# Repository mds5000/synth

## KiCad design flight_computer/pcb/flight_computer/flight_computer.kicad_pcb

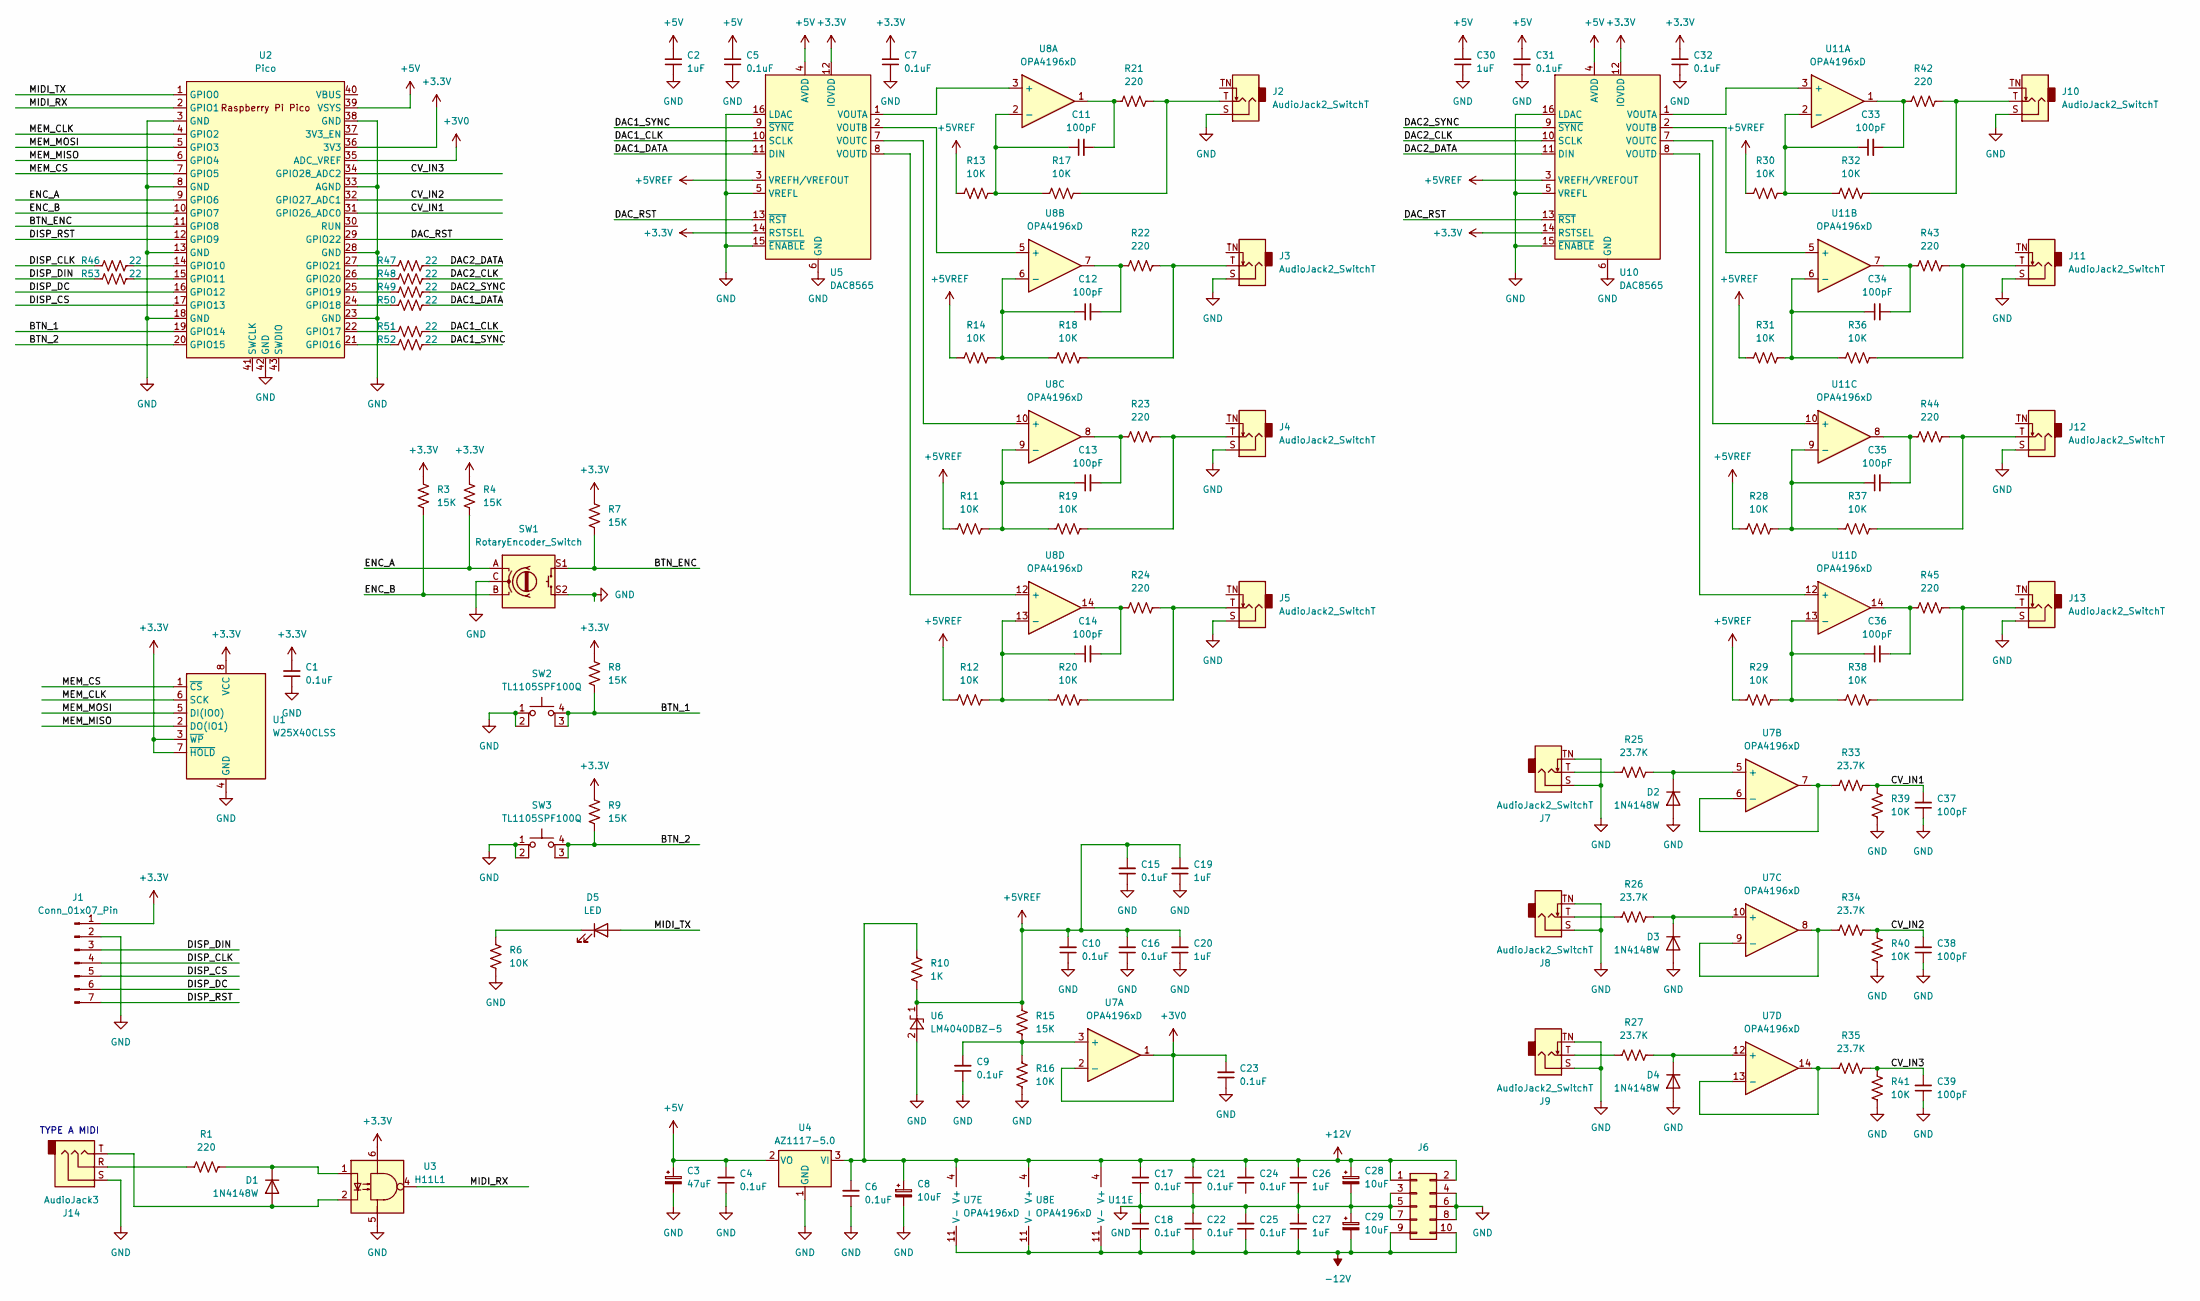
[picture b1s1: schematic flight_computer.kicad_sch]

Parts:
C1, C4, C5, C6, C7, C9, C10, C15, C16, C17, C18, C21, C22, C23, C24, C25, C31, C32: 0.1uF; C_0603_1608Metric
C2, C19, C20, C26, C27, C30: 1uF; C_0603_1608Metric
C3: 47uF; CP_Radial_D5.0mm_P2.00mm
C8, C28, C29: 10uF; CP_Radial_D5.0mm_P2.00mm
C11, C12, C13, C14, C33, C34, C35, C36, C37, C38, C39: 100pF; C_0603_1608Metric
D1, D2, D3, D4: 1N4148W; D_SOD-123
D5: LED
J1: Conn_01x07_Pin; PinHeader_1x07_P2.54mm_Vertical
J2, J3, J4, J5, J7, J8, J9, J10, J11, J12, J13: AudioJack2_SwitchT; Jack_3.5mm_QingPu_WQP-PJ398SM_Vertical_CircularHoles
J6: Conn_02x05_Odd_Even; PinHeader_2x05_P2.54mm_Vertical
J14: AudioJack3
R1, R21, R22, R23, R24, R42, R43, R44, R45: 220; R_0603_1608Metric
R3, R4, R7, R8, R9, R15: 15K; R_0603_1608Metric
R6, R11, R12, R13, R14, R16, R17, R18, R19, R20, R28, R29, R30, R31, R32, R36, R37, R38, R39, R40, R41: 10K; R_0603_1608Metric
R10: 1K; R_0603_1608Metric
R25, R26, R27, R33, R34, R35: 23.7K; R_0603_1608Metric
R46, R47, R48, R49, R50, R51, R52, R53: 22; R_0603_1608Metric
SW1: RotaryEncoder_Switch; RotaryEncoder_Alps_EC12E-Switch_Vertical_H20mm
SW2, SW3: TL1105SPF100Q; SW_PUSH_6mm_H7.3mm
U1: W25X40CLSS; SOIC-8_5.275x5.275mm_P1.27mm
U2: Pico; RPi_Pico_SMD_TH
U3: H11L1; DIP-6_W7.62mm_SMDSocket_SmallPads
U4: AZ1117-5.0; TO-252-2
U5, U10: DAC8565; TSSOP-16_4.4x5mm_P0.65mm
U6: LM4040DBZ-5; SOT-23
U7, U8, U11: OPA4196xD; SOIC-14_3.9x8.7mm_P1.27mm

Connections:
+3.3V: C1.2, C7.2, C32.2, J1.1, R3.2, R4.2, R7.2, R8.2, R9.2, U1.3 (~WP), U1.7 (~HOLD), U1.8 (VCC), U2.36 (3V3), U3.6, U5.12 (IOVDD), U5.14 (RSTSEL), U10.12 (IOVDD), U10.14 (RSTSEL)
+3V0: C23.2, U2.35 (ADC_VREF), U7.1, U7.2 (-)
+5V: C2.2, C3.1, C4.2, C5.2, C30.2, C31.2, U2.39 (VSYS), U4.2 (VO), U5.4 (AVDD), U10.4 (AVDD); also elsewhere on the board
+5VREF: C10.2, C15.2, C16.2, C19.2, C20.2, R10.1, R11.1, R12.1, R13.1, R14.1, R15.2, R28.1, R29.1, R30.1, R31.1, U5.3 (VREFH/VREFOUT), U6.1 (K), U10.3 (VREFH/VREFOUT)
+12V: C6.2, C8.1, C17.2, C21.2, C24.2, C26.2, C28.1, J6.1, J6.2, R10.2, U4.3 (VI), U7.4 (V+), U8.4 (V+), U11.4 (V+)
-12V: C18.1, C22.1, C25.1, C27.1, C29.2, J6.9, J6.10, U7.11 (V-), U8.11 (V-), U11.11 (V-)
/BTN_1: R8.1, SW2.3 (K), SW2.4 (A), U2.19 (GPIO14)
/BTN_2: R9.1, SW3.3 (K), SW3.4 (A), U2.20 (GPIO15)
/BTN_ENC: R7.1, SW1.S1, U2.11 (GPIO8)
/CV_IN1: C37.2, R33.2, R39.2, U2.31 (GPIO26_ADC0)
/CV_IN2: C38.2, R34.2, R40.2, U2.32 (GPIO27_ADC1)
/CV_IN3: C39.2, R35.2, R41.2, U2.34 (GPIO28_ADC2)
/DAC1_CLK: R51.2, U5.10 (SCLK)
/DAC1_DATA: R50.2, U5.11 (DIN)
/DAC1_SYNC: R52.2, U5.9 (~SYNC)
/DAC2_CLK: R48.2, U10.10 (SCLK)
/DAC2_DATA: R47.2, U10.11 (DIN)
/DAC2_SYNC: R49.2, U10.9 (~SYNC)
/DAC_RST: U2.29 (GPIO22), U5.13 (~RST), U10.13 (~RST)
/DISP_CLK: J1.4, R46.1
/DISP_CS: J1.5, U2.17 (GPIO13)
/DISP_DC: J1.6, U2.16 (GPIO12)
/DISP_DIN: J1.3, R53.1
/DISP_RST: J1.7, U2.12 (GPIO9)
/ENC_A: R4.1, SW1.A, U2.9 (GPIO6)
/ENC_B: R3.1, SW1.B, U2.10 (GPIO7)
/MEM_CLK: U1.6 (SCK), U2.4 (GPIO2)
/MEM_CS: U1.1 (~CS), U2.7 (GPIO5)
/MEM_MISO: U1.2 (DO(IO1)), U2.6 (GPIO4)
/MEM_MOSI: U1.5 (DI(IO0)), U2.5 (GPIO3)
/MIDI_RX: U2.2 (GPIO1), U3.4
/MIDI_TX: D5.1 (K), D5.2 (A), R6.1, U2.1 (GPIO0); also elsewhere on the board
GND: C1.1, C2.1, C3.2, C4.1, C5.1, C6.1, C7.1, C8.2, C9.1, C10.1, C15.1, C16.1, C17.1, C18.2, C19.1, C20.1, C21.1, C22.2, C23.1, C25.2, C26.1, C27.2, C28.2, C29.1, C30.1, C31.1, C32.1, C37.1, C38.1, C39.1, D2.2 (A), D3.2 (A), D4.2 (A), J1.2, J2.S, J3.S, J4.S, J5.S, J6.3, J6.4, J6.5, J6.6, J6.7, J6.8, J7.S, J7.TN, J8.S, J8.TN, J9.S, J9.TN, J10.S, J11.S, J12.S, J13.S, J14.S, R6.2, R16.1, R39.1, R40.1, R41.1, SW1.C, SW1.S2, SW2.1, SW2.2, SW3.1, SW3.2, U1.4 (GND), U2.3 (GND), U2.8 (GND), U2.13 (GND), U2.18 (GND), U2.23 (GND), U2.28 (GND), U2.33 (AGND), U2.38 (GND), U2.42 (GND), U3.5, U4.1 (GND), U5.5 (VREFL), U5.6 (GND), U5.15 (~ENABLE), U5.16 (LDAC), U6.2 (A), U10.5 (VREFL), U10.6 (GND), U10.15 (~ENABLE), U10.16 (LDAC); also elsewhere on the board
unnamed: C11.2, R21.1, U8.1
unnamed: C12.2, R22.1, U8.7
unnamed: C13.2, R23.1, U8.8
unnamed: C14.2, R24.1, U8.14
unnamed: C33.2, R42.1, U11.1
unnamed: C34.2, R43.1, U11.7
unnamed: C35.2, R44.1, U11.8
unnamed: C36.2, R45.1, U11.14
unnamed: D1.2 (A), J14.T, U3.2
unnamed: D1.1 (K), R1.2, U3.1
unnamed: D2.1 (K), R25.2, U7.5 (+)
unnamed: D3.1 (K), R26.2, U7.10 (+)
unnamed: D4.1 (K), R27.2, U7.12 (+)
unnamed: J2.T, R17.2, R21.2
unnamed: J3.T, R18.2, R22.2
unnamed: J4.T, R19.2, R23.2
unnamed: J5.T, R20.2, R24.2
unnamed: J7.T, R25.1
unnamed: J8.T, R26.1
unnamed: J9.T, R27.1
unnamed: J10.T, R32.2, R42.2
unnamed: J11.T, R36.2, R43.2
unnamed: J12.T, R37.2, R44.2
unnamed: J13.T, R38.2, R45.2
unnamed: J14.R, R1.1
unnamed: R46.2, U2.14 (GPIO10)
unnamed: R53.2, U2.15 (GPIO11)
unnamed: R52.1, U2.21 (GPIO16)
unnamed: R51.1, U2.22 (GPIO17)
unnamed: R50.1, U2.24 (GPIO18)
unnamed: R49.1, U2.25 (GPIO19)
unnamed: R48.1, U2.26 (GPIO20)
unnamed: R47.1, U2.27 (GPIO21)
unnamed: U5.1 (VOUTA), U8.3 (+)
unnamed: U5.2 (VOUTB), U8.5 (+)
unnamed: U5.7 (VOUTC), U8.10 (+)
unnamed: U5.8 (VOUTD), U8.12 (+)
unnamed: C9.2, R15.1, R16.2, U7.3 (+)
unnamed: R33.1, U7.6 (-), U7.7
unnamed: R34.1, U7.8, U7.9 (-)
unnamed: R35.1, U7.13 (-), U7.14
unnamed: C11.1, R13.2, R17.1, U8.2 (-)
unnamed: C12.1, R14.2, R18.1, U8.6 (-)
unnamed: C13.1, R11.2, R19.1, U8.9 (-)
unnamed: C14.1, R12.2, R20.1, U8.13 (-)
unnamed: U10.1 (VOUTA), U11.3 (+)
unnamed: U10.2 (VOUTB), U11.5 (+)
unnamed: U10.7 (VOUTC), U11.10 (+)
unnamed: U10.8 (VOUTD), U11.12 (+)
unnamed: C33.1, R30.2, R32.1, U11.2 (-)
unnamed: C34.1, R31.2, R36.1, U11.6 (-)
unnamed: C35.1, R28.2, R37.1, U11.9 (-)
unnamed: C36.1, R29.2, R38.1, U11.13 (-)

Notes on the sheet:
TYPE A MIDI

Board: 2 copper layers, 123 parts (5 on the bottom side), 86 nets, no tracks yet.

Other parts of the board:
Q1: MMBT3904; SOT-23
R2: 220; R_0603_1608Metric
R5: 1K; R_0603_1608Metric

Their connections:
+5V: R5.2; also elsewhere on the board
/MIDI_TX: Q1.1 (B); also elsewhere on the board
GND: Q1.2 (E); also elsewhere on the board
unnamed: Q1.3 (C), R2.2, R5.1

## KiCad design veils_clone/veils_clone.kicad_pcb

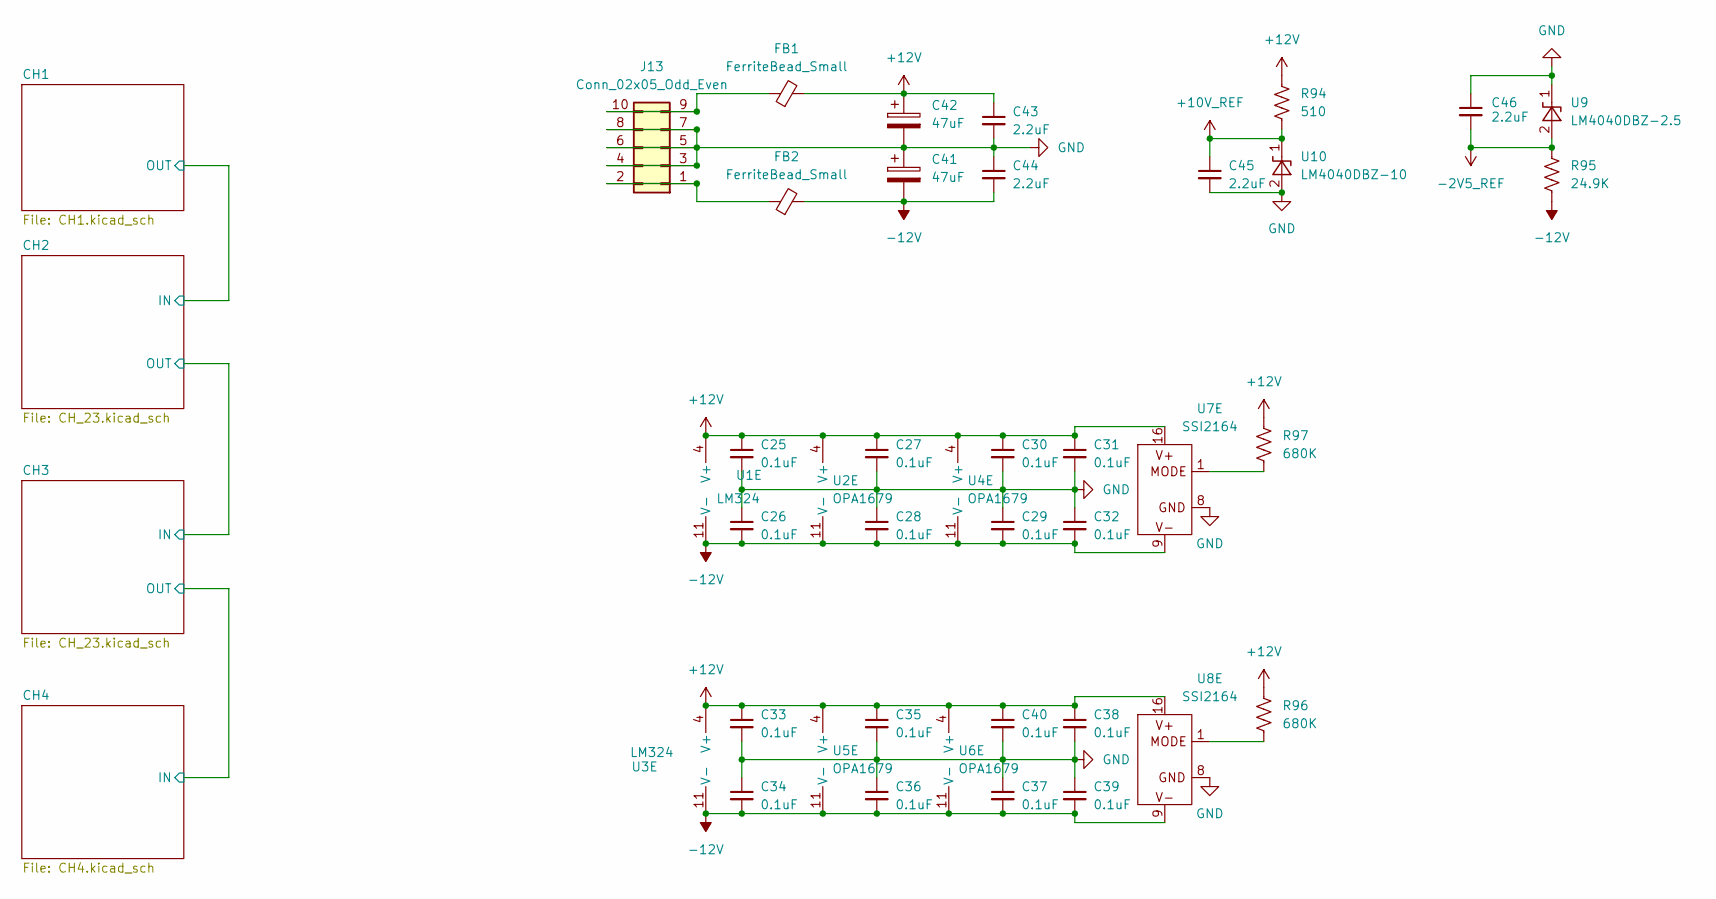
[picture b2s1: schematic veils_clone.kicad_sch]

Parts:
C25, C26, C27, C28, C29, C30, C31, C32, C33, C34, C35, C36, C37, C38, C39, C40: 0.1uF; C_0603_1608Metric
C41, C42: 47uF; CP_Radial_D5.0mm_P2.00mm
C43, C44, C45, C46: 2.2uF; C_0603_1608Metric
FB1, FB2: FerriteBead_Small; C_0603_1608Metric
J13: Conn_02x05_Odd_Even; PinHeader_2x05_P2.54mm_Vertical_SMD
R94: 510; R_0603_1608Metric
R95: 24.9K; R_0603_1608Metric
R96, R97: 680K; R_0603_1608Metric
U1, U3: LM324; TSSOP-14_4.4x5mm_P0.65mm
U2, U4, U5, U6: OPA1679; TSSOP-14_4.4x5mm_P0.65mm
U7, U8: SSI2164; SOIC-16_3.9x9.9mm_P1.27mm
U9: LM4040DBZ-2.5; SOT-23
U10: LM4040DBZ-10; SOT-23

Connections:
+10V_REF: C45.1, R94.1, U10.1 (K); also elsewhere on the board
+12V: C25.1, C27.1, C30.1, C31.1, C33.1, C35.1, C38.1, C40.1, C42.1, C43.1, FB1.2, R94.2, R96.2, R97.2, U1.4 (V+), U2.4 (V+), U3.4 (V+), U4.4 (V+), U5.4 (V+), U6.4 (V+), U7.16 (V+), U8.16 (V+)
-2V5_REF: C46.2, R95.2, U9.2 (A); also elsewhere on the board
-12V: C26.2, C28.2, C29.2, C32.2, C34.2, C36.2, C37.2, C39.2, C41.2, C44.2, FB2.2, R95.1, U1.11 (V-), U2.11 (V-), U3.11 (V-), U4.11 (V-), U5.11 (V-), U6.11 (V-), U7.9 (V-), U8.9 (V-)
GND: C25.2, C26.1, C27.2, C28.1, C29.1, C30.2, C31.2, C32.1, C33.2, C34.1, C35.2, C36.1, C37.1, C38.2, C39.1, C40.2, C41.1, C42.2, C43.2, C44.1, C45.2, C46.1, J13.3, J13.4, J13.5, J13.6, J13.7, J13.8, U3.5 (+), U7.8 (GND), U8.8 (GND), U9.1 (K), U10.2 (A); also elsewhere on the board
unnamed 38: U3.2 (-); also elsewhere on the board
unnamed 39: U3.1; also elsewhere on the board
unnamed: FB2.1, J13.1, J13.2
unnamed: FB1.1, J13.9, J13.10
unnamed 73: U3.7; also elsewhere on the board
unnamed 85: U3.3 (+); also elsewhere on the board
unnamed 86: U3.6 (-); also elsewhere on the board
unnamed 93: U8.4 (OUTA); also elsewhere on the board
unnamed 94: U8.5 (OUTB); also elsewhere on the board
unnamed: R97.1, U7.1 (MODE)
unnamed 110: U8.3 (CVA); also elsewhere on the board
unnamed 111: U8.2 (INA); also elsewhere on the board
unnamed 112: U8.6 (CVB); also elsewhere on the board
unnamed 113: U8.7 (INB); also elsewhere on the board
unnamed: R96.1, U8.1 (MODE)

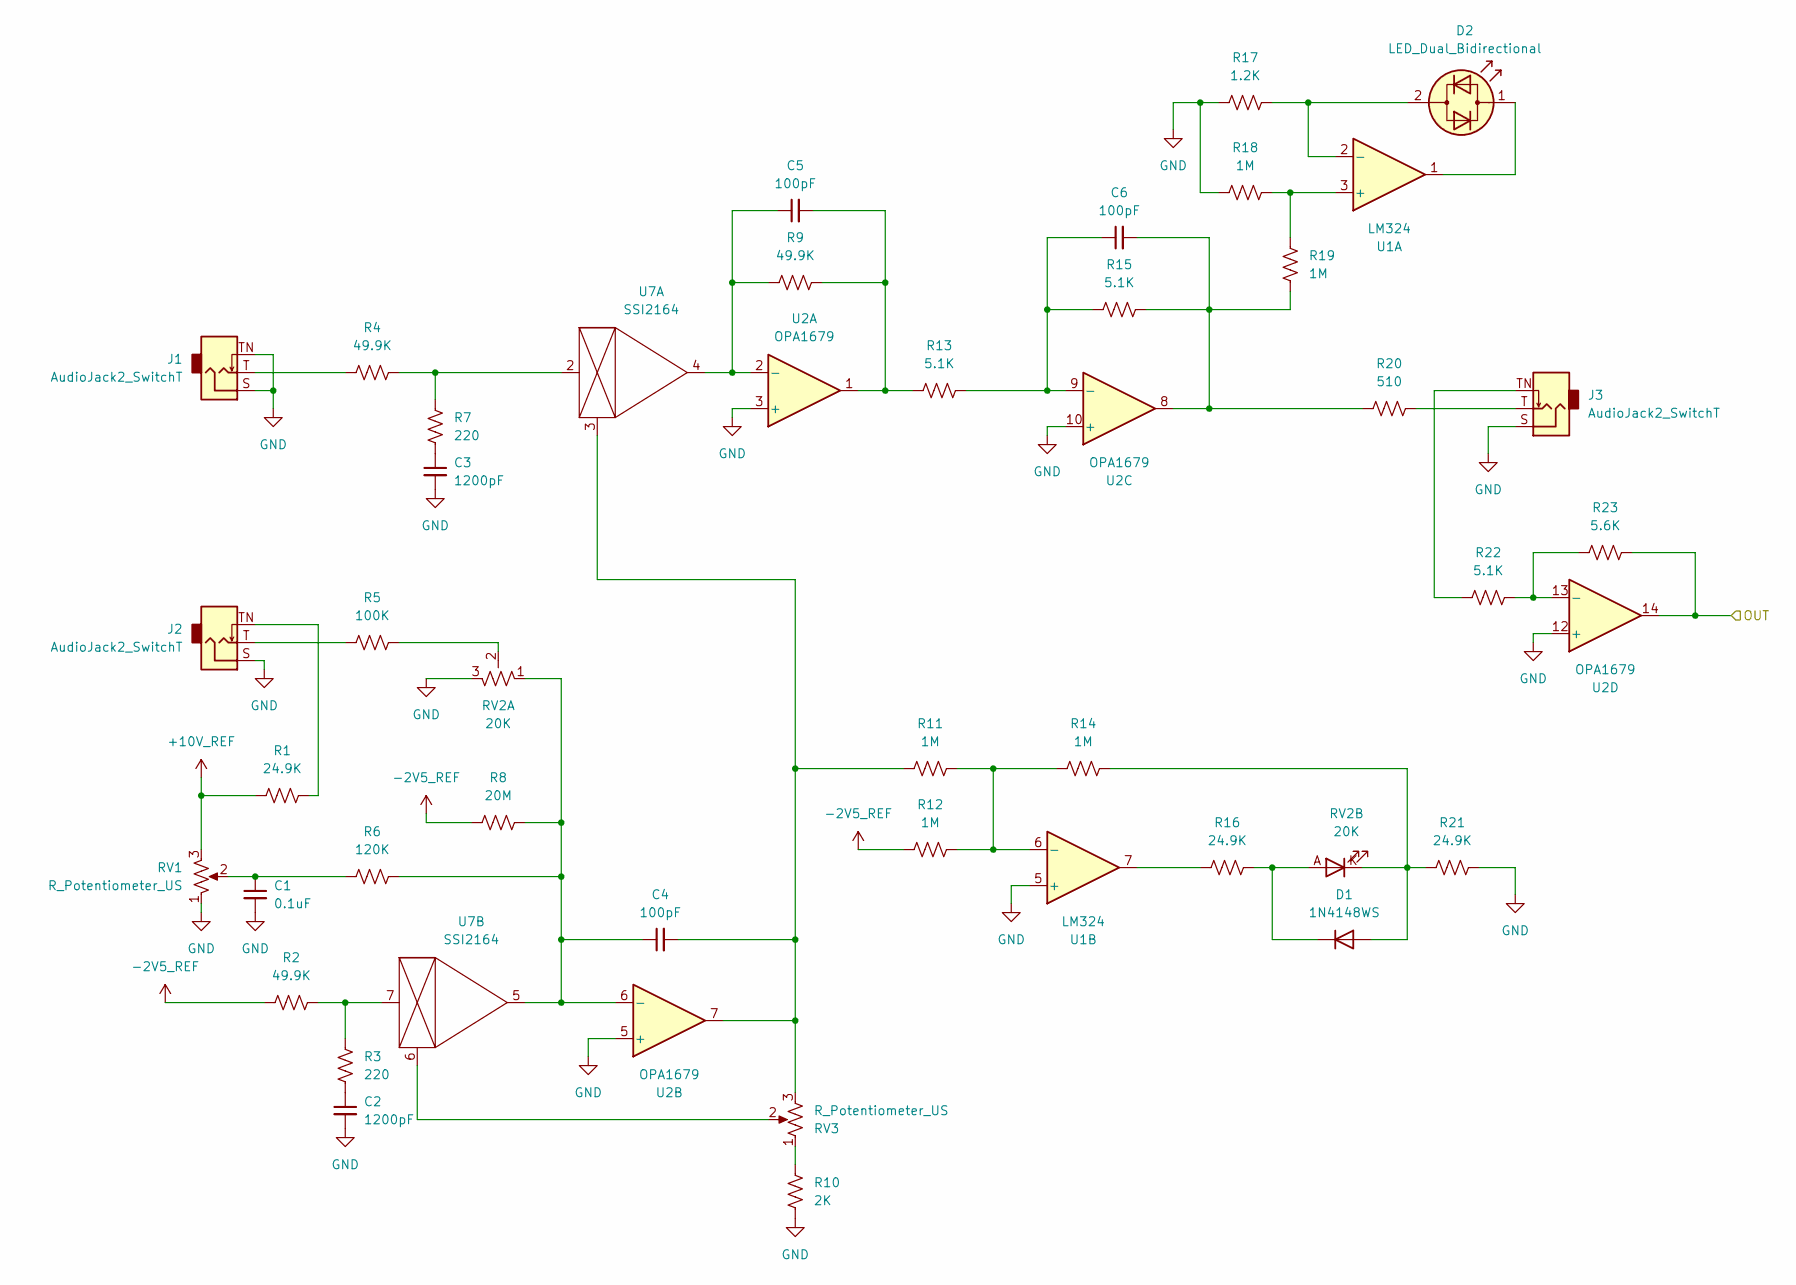
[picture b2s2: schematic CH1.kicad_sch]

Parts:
C1: 0.1uF; C_0603_1608Metric
C2, C3: 1200pF; C_0603_1608Metric
C4, C5, C6: 100pF; C_0603_1608Metric
D1: 1N4148WS; D_SOD-323
D2: LED_Dual_Bidirectional; LED_D3.0mm
J1, J2: AudioJack2_SwitchT; Jack_3.5mm_QingPu_WQP-PJ398SM_Vertical_CircularHoles
J3: AudioJack2_SwitchT; Jack_3.5mm_QingPu_WQP-PJ398SM_Vertical_NoRing
R1, R16, R21: 24.9K; R_0603_1608Metric
R2, R4, R9: 49.9K; R_0603_1608Metric
R3, R7: 220; R_0603_1608Metric
R5: 100K; R_0603_1608Metric
R6: 120K; R_0603_1608Metric
R8: 20M; R_0603_1608Metric
R10: 2K; R_0603_1608Metric
R11, R12, R14, R18, R19: 1M; R_0603_1608Metric
R13, R15, R22: 5.1K; R_0603_1608Metric
R17: 1.2K; R_0603_1608Metric
R20: 510; R_0603_1608Metric
R23: 5.6K; R_0603_1608Metric
RV1, RV3: R_Potentiometer_US; Potentiometer_Alpha_RV09AF-40-00D_Single_Vertical
RV2: 20K; PTL20-15G1-203B2
U1: LM324; TSSOP-14_4.4x5mm_P0.65mm
U2: OPA1679; TSSOP-14_4.4x5mm_P0.65mm
U7: SSI2164; SOIC-16_3.9x9.9mm_P1.27mm

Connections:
+10V_REF: R1.1, RV1.3; also elsewhere on the board
-2V5_REF: R2.1, R8.1, R12.1; also elsewhere on the board
/CH1/OUT: R23.2, U2.14; also elsewhere on the board
GND: C1.2, C2.2, C3.2, J1.S, J1.TN, J2.S, J3.S, R10.1, R17.1, R18.1, R21.2, RV1.1, RV2.3, U1.5 (+), U2.3 (+), U2.5 (+), U2.10 (+), U2.12 (+); also elsewhere on the board
unnamed: C1.1, R6.1, RV1.2
unnamed: C2.1, R3.1
unnamed: C3.1, R7.1
unnamed: C5.2, R9.2, R13.1, U2.1
unnamed: C6.2, R15.2, R19.1, R20.1, U2.8
unnamed: D1.2 (A), R14.2, R21.1, RV2.K
unnamed: D1.1 (K), R16.2, RV2.A
unnamed: D2.2 (AK), R17.2, U1.2 (-)
unnamed: D2.1 (KA), U1.1
unnamed: J1.T, R4.1
unnamed: J2.T, R5.1
unnamed: J2.TN, R1.2
unnamed: J3.T, R20.2
unnamed: J3.TN, R22.1
unnamed: R5.2, RV2.2
unnamed: R10.2, RV3.1
unnamed: R16.1, U1.7
unnamed: R18.2, R19.2, U1.3 (+)
unnamed: R11.2, R12.2, R14.1, U1.6 (-)
unnamed: C5.1, R9.1, U2.2 (-), U7.4 (OUTA)
unnamed: C4.1, R6.2, R8.2, RV2.1, U2.6 (-), U7.5 (OUTB)
unnamed: C6.1, R13.2, R15.1, U2.9 (-)
unnamed: R22.2, R23.1, U2.13 (-)
unnamed: C4.2, R11.1, RV3.3, U2.7, U7.3 (CVA)
unnamed: R4.2, R7.2, U7.2 (INA)
unnamed: RV3.2, U7.6 (CVB)
unnamed: R2.2, R3.2, U7.7 (INB)

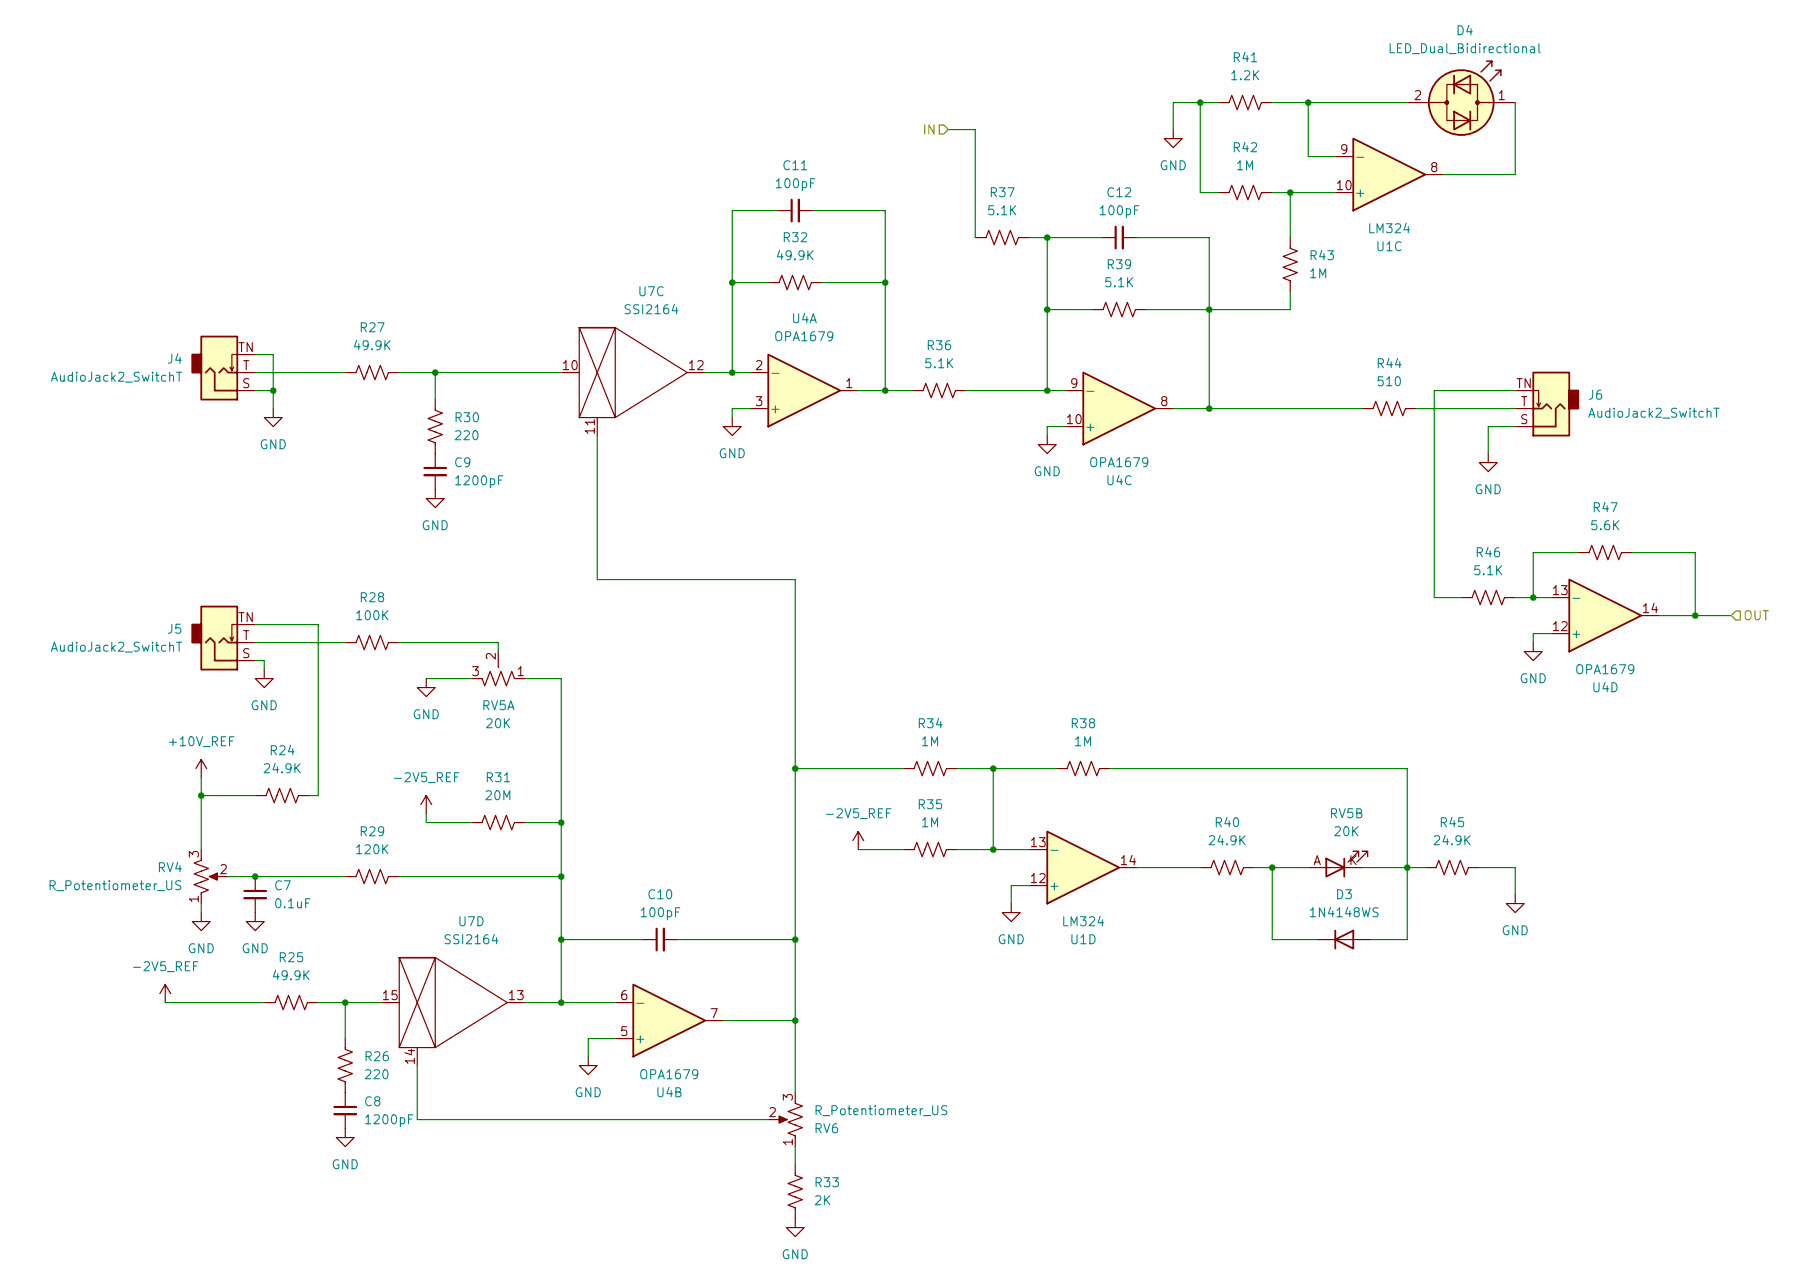
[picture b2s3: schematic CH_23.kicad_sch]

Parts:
C7: 0.1uF; C_0603_1608Metric
C8, C9: 1200pF; C_0603_1608Metric
C10, C11, C12: 100pF; C_0603_1608Metric
D3: 1N4148WS; D_SOD-323
D4: LED_Dual_Bidirectional; LED_D3.0mm
J4, J5: AudioJack2_SwitchT; Jack_3.5mm_QingPu_WQP-PJ398SM_Vertical_CircularHoles
J6: AudioJack2_SwitchT; Jack_3.5mm_QingPu_WQP-PJ398SM_Vertical_NoRing
R24, R40, R45: 24.9K; R_0603_1608Metric
R25, R27, R32: 49.9K; R_0603_1608Metric
R26, R30: 220; R_0603_1608Metric
R28: 100K; R_0603_1608Metric
R29: 120K; R_0603_1608Metric
R31: 20M; R_0603_1608Metric
R33: 2K; R_0603_1608Metric
R34, R35, R38, R42, R43: 1M; R_0603_1608Metric
R36, R37, R39, R46: 5.1K; R_0603_1608Metric
R41: 1.2K; R_0603_1608Metric
R44: 510; R_0603_1608Metric
R47: 5.6K; R_0603_1608Metric
RV4, RV6: R_Potentiometer_US; Potentiometer_Alpha_RV09AF-40-00D_Single_Vertical
RV5: 20K; PTL20-15G1-203B2
U1: LM324; TSSOP-14_4.4x5mm_P0.65mm
U4: OPA1679; TSSOP-14_4.4x5mm_P0.65mm
U7: SSI2164; SOIC-16_3.9x9.9mm_P1.27mm

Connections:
+10V_REF: R24.1, RV4.3; also elsewhere on the board
-2V5_REF: R25.1, R31.1, R35.1; also elsewhere on the board
/CH1/OUT: R37.1; also elsewhere on the board
/CH2/OUT: R47.2, U4.14; also elsewhere on the board
GND: C7.2, C8.2, C9.2, J4.S, J4.TN, J5.S, J6.S, R33.1, R41.1, R42.1, R45.2, RV4.1, RV5.3, U1.12 (+), U4.3 (+), U4.5 (+), U4.10 (+), U4.12 (+); also elsewhere on the board
unnamed: C7.1, R29.1, RV4.2
unnamed: C8.1, R26.1
unnamed: C9.1, R30.1
unnamed: C11.2, R32.2, R36.1, U4.1
unnamed: C12.2, R39.2, R43.1, R44.1, U4.8
unnamed: D3.2 (A), R38.2, R45.1, RV5.K
unnamed: D3.1 (K), R40.2, RV5.A
unnamed: D4.2 (AK), R41.2, U1.9 (-)
unnamed: D4.1 (KA), U1.8
unnamed: J4.T, R27.1
unnamed: J5.T, R28.1
unnamed: J5.TN, R24.2
unnamed: J6.T, R44.2
unnamed: J6.TN, R46.1
unnamed: R28.2, RV5.2
unnamed: R33.2, RV6.1
unnamed: R40.1, U1.14
unnamed: R42.2, R43.2, U1.10 (+)
unnamed: R34.2, R35.2, R38.1, U1.13 (-)
unnamed: C11.1, R32.1, U4.2 (-), U7.12 (OUTC)
unnamed: C10.1, R29.2, R31.2, RV5.1, U4.6 (-), U7.13 (OUTD)
unnamed: C12.1, R36.2, R37.2, R39.1, U4.9 (-)
unnamed: R46.2, R47.1, U4.13 (-)
unnamed: C10.2, R34.1, RV6.3, U4.7, U7.11 (CVC)
unnamed: R27.2, R30.2, U7.10 (INC)
unnamed: RV6.2, U7.14 (CVD)
unnamed: R25.2, R26.2, U7.15 (IND)

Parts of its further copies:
C13: 0.1uF; C_0603_1608Metric
C14, C15: 1200pF; C_0603_1608Metric
C16, C17, C18: 100pF; C_0603_1608Metric
D5: 1N4148WS; D_SOD-323
D6: LED_Dual_Bidirectional; LED_D3.0mm
J7, J8: AudioJack2_SwitchT; Jack_3.5mm_QingPu_WQP-PJ398SM_Vertical_CircularHoles
J9: AudioJack2_SwitchT; Jack_3.5mm_QingPu_WQP-PJ398SM_Vertical_NoRing
R48, R64, R69: 24.9K; R_0603_1608Metric
R49, R51, R56: 49.9K; R_0603_1608Metric
R50, R54: 220; R_0603_1608Metric
R52: 100K; R_0603_1608Metric
R53: 120K; R_0603_1608Metric
R55: 20M; R_0603_1608Metric
R57: 2K; R_0603_1608Metric
R58, R59, R62, R66, R67: 1M; R_0603_1608Metric
R60, R61, R63, R70: 5.1K; R_0603_1608Metric
R65: 1.2K; R_0603_1608Metric
R68: 510; R_0603_1608Metric
RV7, RV9: R_Potentiometer_US; Potentiometer_Alpha_RV09AF-40-00D_Single_Vertical
RV8: 20K; PTL20-15G1-203B2

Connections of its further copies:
+10V_REF: R48.1, RV7.3; also elsewhere on the board
-2V5_REF: R49.1, R55.1, R59.1; also elsewhere on the board
/CH2/OUT: R61.1; also elsewhere on the board
GND: C13.2, C14.2, C15.2, J7.S, J7.TN, J8.S, R57.1, R65.1, R66.1, R69.2, RV7.1, RV8.3; also elsewhere on the board
unnamed: C13.1, R53.1, RV7.2
unnamed: C14.1, R50.1
unnamed: C15.1, R54.1
unnamed 21: C17.2, R56.2, R60.1; also elsewhere on the board
unnamed 22: C18.2, R63.2, R67.1, R68.1; also elsewhere on the board
unnamed: D5.2 (A), R62.2, R69.1, RV8.K
unnamed: D5.1 (K), R64.2, RV8.A
unnamed 38: D6.2 (AK), R65.2; also elsewhere on the board
unnamed 39: D6.1 (KA); also elsewhere on the board
unnamed: J7.T, R51.1
unnamed: J8.T, R52.1
unnamed: J8.TN, R48.2
unnamed: J9.T, R68.2
unnamed: J9.TN, R70.1
unnamed: R52.2, RV8.2
unnamed: R57.2, RV9.1
unnamed 73: R64.1; also elsewhere on the board
unnamed 85: R66.2, R67.2; also elsewhere on the board
unnamed 86: R58.2, R59.2, R62.1; also elsewhere on the board
unnamed 93: C17.1, R56.1; also elsewhere on the board
unnamed 94: C16.1, R53.2, R55.2, RV8.1; also elsewhere on the board
unnamed 95: C18.1, R60.2, R61.2, R63.1; also elsewhere on the board
unnamed 96: R70.2; also elsewhere on the board
unnamed 110: C16.2, R58.1, RV9.3; also elsewhere on the board
unnamed 111: R51.2, R54.2; also elsewhere on the board
unnamed 112: RV9.2; also elsewhere on the board
unnamed 113: R49.2, R50.2; also elsewhere on the board

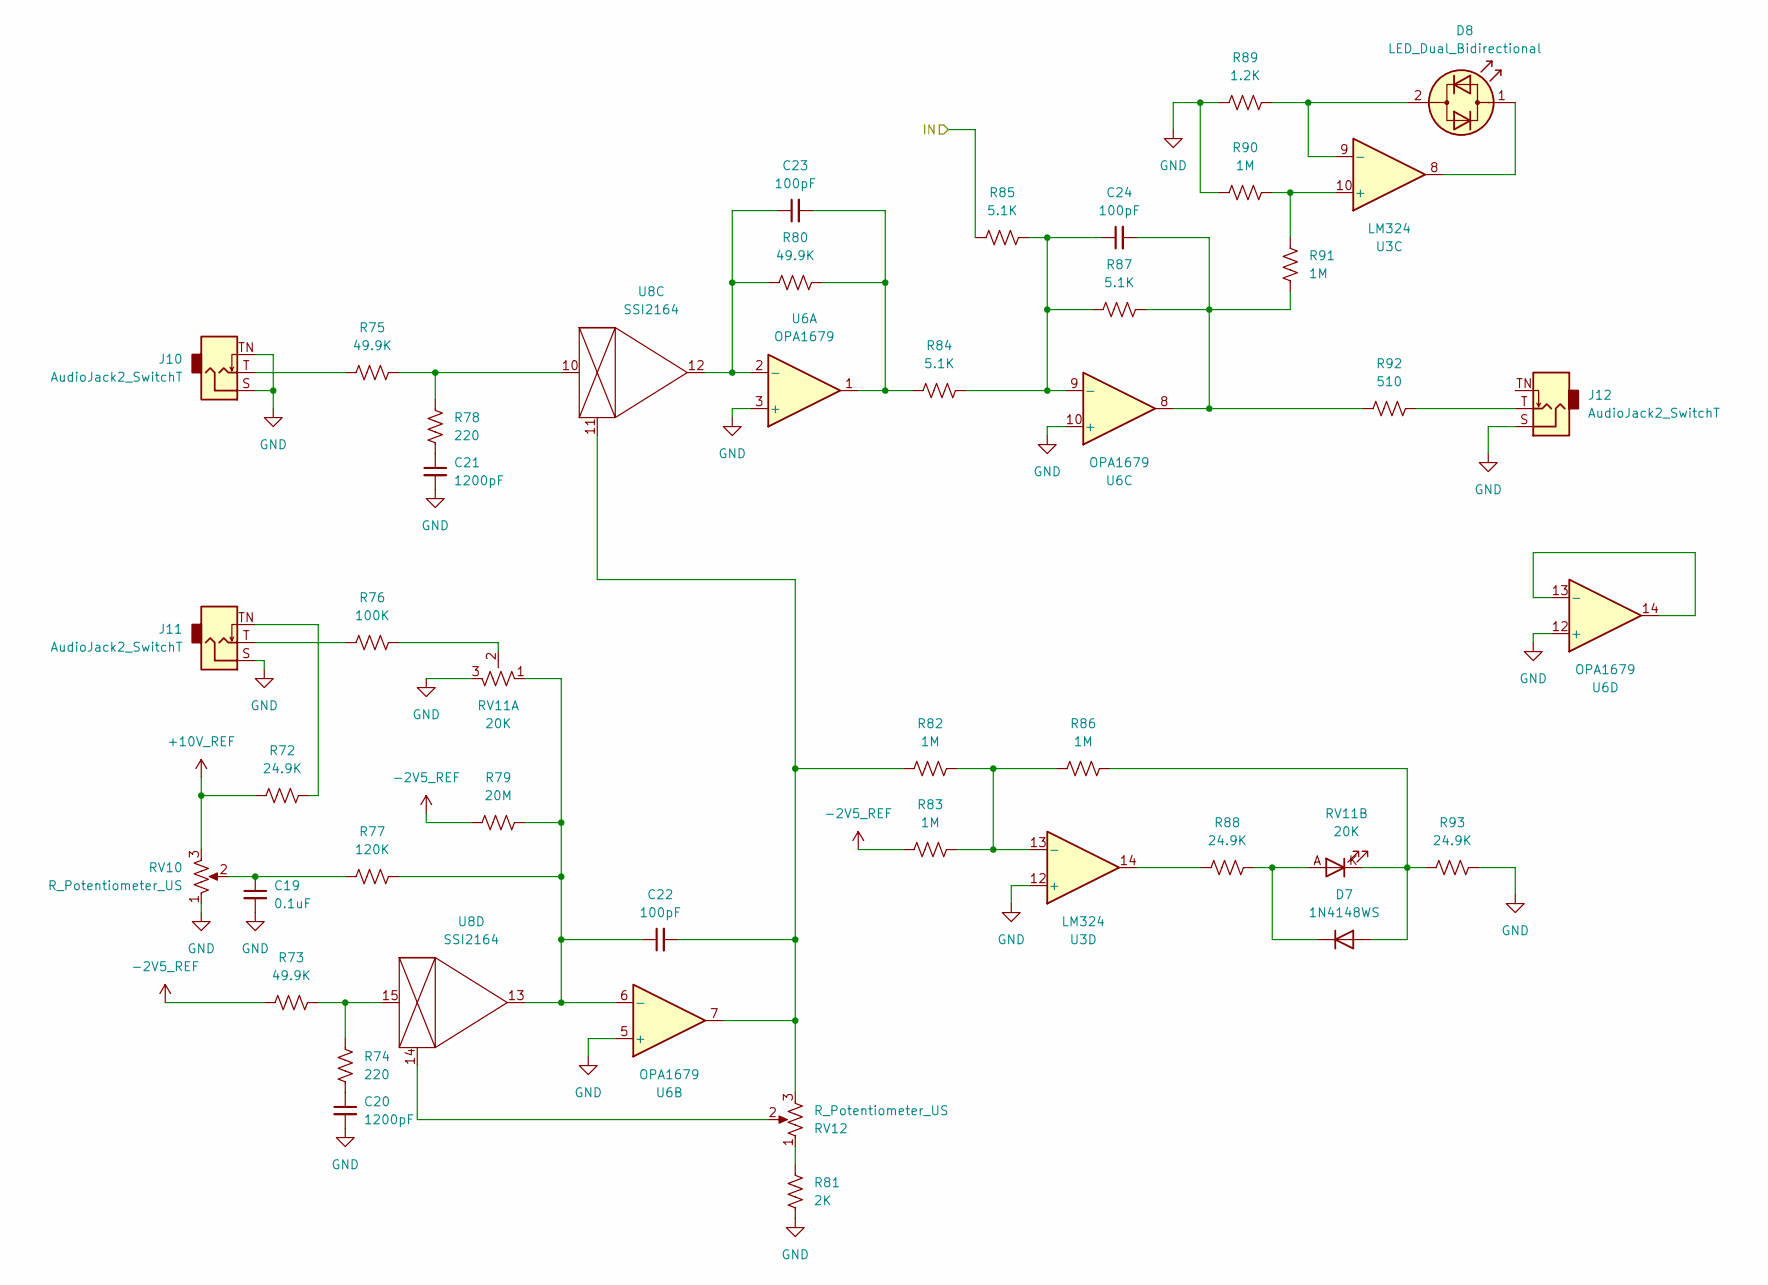
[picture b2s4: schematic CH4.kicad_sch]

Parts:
C19: 0.1uF; C_0603_1608Metric
C20, C21: 1200pF; C_0603_1608Metric
C22, C23, C24: 100pF; C_0603_1608Metric
D7: 1N4148WS; D_SOD-323
D8: LED_Dual_Bidirectional; LED_D3.0mm
J10, J11: AudioJack2_SwitchT; Jack_3.5mm_QingPu_WQP-PJ398SM_Vertical_CircularHoles
J12: AudioJack2_SwitchT; Jack_3.5mm_QingPu_WQP-PJ398SM_Vertical_NoRing
R72, R88, R93: 24.9K; R_0603_1608Metric
R73, R75, R80: 49.9K; R_0603_1608Metric
R74, R78: 220; R_0603_1608Metric
R76: 100K; R_0603_1608Metric
R77: 120K; R_0603_1608Metric
R79: 20M; R_0603_1608Metric
R81: 2K; R_0603_1608Metric
R82, R83, R86, R90, R91: 1M; R_0603_1608Metric
R84, R85, R87: 5.1K; R_0603_1608Metric
R89: 1.2K; R_0603_1608Metric
R92: 510; R_0603_1608Metric
RV10, RV12: R_Potentiometer_US; Potentiometer_Alpha_RV09AF-40-00D_Single_Vertical
RV11: 20K; PTL20-15G1-203B2
U3: LM324; TSSOP-14_4.4x5mm_P0.65mm
U6: OPA1679; TSSOP-14_4.4x5mm_P0.65mm
U8: SSI2164; SOIC-16_3.9x9.9mm_P1.27mm

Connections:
+10V_REF: R72.1, RV10.3; also elsewhere on the board
-2V5_REF: R73.1, R79.1, R83.1; also elsewhere on the board
/CH3/OUT: R85.1; also elsewhere on the board
GND: C19.2, C20.2, C21.2, J10.S, J10.TN, J11.S, J12.S, R81.1, R89.1, R90.1, R93.2, RV10.1, RV11.3, U3.5 (+), U3.12 (+), U6.3 (+), U6.5 (+), U6.10 (+), U6.12 (+); also elsewhere on the board
unnamed: C19.1, R77.1, RV10.2
unnamed: C20.1, R74.1
unnamed: C21.1, R78.1
unnamed: C23.2, R80.2, R84.1, U6.1
unnamed: C24.2, R87.2, R91.1, R92.1, U6.8
unnamed 38: U3.2 (-); also elsewhere on the board
unnamed 39: U3.1; also elsewhere on the board
unnamed: D7.2 (A), R86.2, R93.1, RV11.K
unnamed: D7.1 (K), R88.2, RV11.A
unnamed: D8.2 (AK), R89.2, U3.9 (-)
unnamed: D8.1 (KA), U3.8
unnamed: J10.T, R75.1
unnamed: J11.T, R76.1
unnamed: J11.TN, R72.2
unnamed: J12.T, R92.2
unnamed 73: U3.7; also elsewhere on the board
unnamed: R76.2, RV11.2
unnamed: R81.2, RV12.1
unnamed: R88.1, U3.14
unnamed 85: U3.3 (+); also elsewhere on the board
unnamed 86: U3.6 (-); also elsewhere on the board
unnamed: R90.2, R91.2, U3.10 (+)
unnamed: R82.2, R83.2, R86.1, U3.13 (-)
unnamed 93: U8.4 (OUTA); also elsewhere on the board
unnamed 94: U8.5 (OUTB); also elsewhere on the board
unnamed: C23.1, R80.1, U6.2 (-), U8.12 (OUTC)
unnamed: C22.1, R77.2, R79.2, RV11.1, U6.6 (-), U8.13 (OUTD)
unnamed: C24.1, R84.2, R85.2, R87.1, U6.9 (-)
unnamed: U6.13 (-), U6.14
unnamed 110: U8.3 (CVA); also elsewhere on the board
unnamed 111: U8.2 (INA); also elsewhere on the board
unnamed 112: U8.6 (CVB); also elsewhere on the board
unnamed 113: U8.7 (INB); also elsewhere on the board
unnamed: C22.2, R82.1, RV12.3, U6.7, U8.11 (CVC)
unnamed: R75.2, R78.2, U8.10 (INC)
unnamed: RV12.2, U8.14 (CVD)
unnamed: R73.2, R74.2, U8.15 (IND)
